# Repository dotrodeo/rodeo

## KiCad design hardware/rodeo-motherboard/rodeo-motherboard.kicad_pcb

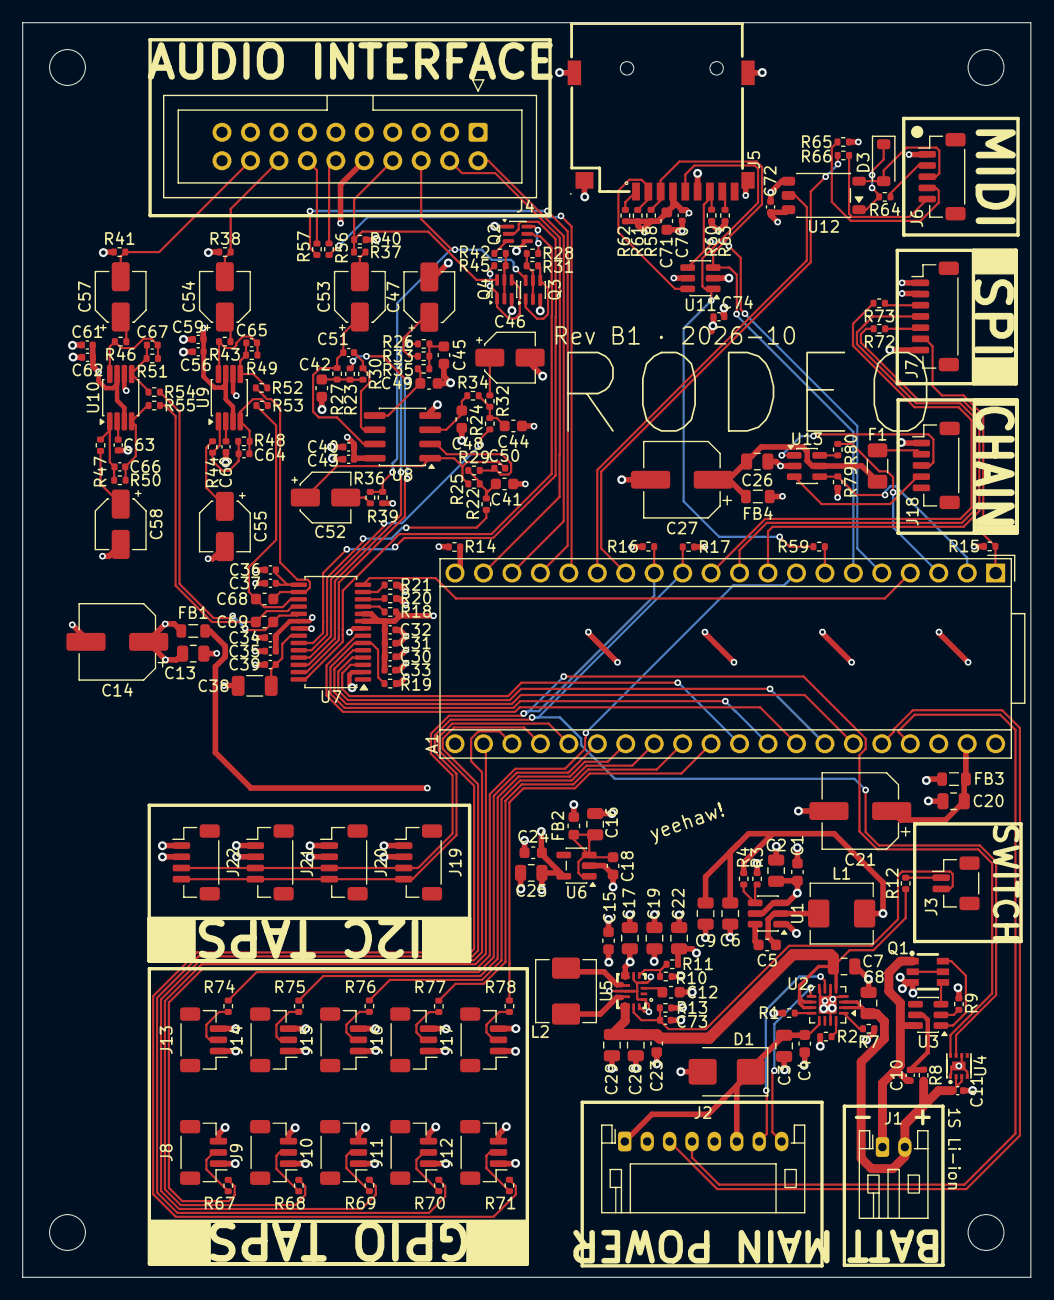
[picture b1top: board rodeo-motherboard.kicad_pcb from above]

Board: 4 copper layers, 90.0 x 112.0 mm, 205 parts (0 on the bottom side), 147 nets.

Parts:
A1: Electrosmith_Daisy_Seed_Rev4; Electrosmith_Daisy_Seed
C1, C5: 0.1u; C_0603_1608Metric
C2, C3, C13, C16, C20, C25, C26, C28, C29: 10u; C_0805_2012Metric
C4, C18, C24: 1u; C_0603_1608Metric
C6, C9, C17, C19, C22: 22u; C_0805_2012Metric
C7, C8: 4.7u; C_0805_2012Metric
C10, C30, C32, C34, C37, C39, C43, C59, C60, C62, C63, C70, C72, C74: 0.1u; C_0402_1005Metric
C11, C31, C33, C35, C36, C40, C56, C61: 1u; C_0402_1005Metric
C12: 100n; C_0603_1608Metric
C14, C21, C27: 100u; CP_Elec_6.3x5.4
C15, C23, C71: 10u; C_0603_1608Metric
C38: 47u; C_1206_3216Metric
C41, C42: 2.2n; C_0603_1608Metric
C44, C45: 6.8n; C_0603_1608Metric
C46, C47, C52, C53: 22u; CP_Elec_4x5.4
C48, C49: 1.5n; C_0603_1608Metric
C50, C51: 470p; C_0402_1005Metric
C54, C55, C57, C58: 10u; CP_Elec_4x5.4
C64, C65, C66, C67: 150p; C_0402_1005Metric
C68, C69: 2.7n; C_0603_1608Metric
C73: 10n; C_0402_1005Metric
D1: SMBJ5.0A; D_SMB
D3: 1N4148W; D_SOD-123
F1: nSMD075; Fuse_1206_3216Metric
FB1, FB3, FB4: BLM21PG221SN1D; L_0805_2012Metric
FB2: BLM18KG601SN1D; L_0603_1608Metric
H1, H2, H3, H4: MountingHole; MountingHole_3.2mm_M3
J1: Conn_01x02; JST_PH_S2B-PH-K_1x02_P2.00mm_Horizontal
J2: Conn_01x08; JST_PH_S8B-PH-K_1x08_P2.00mm_Horizontal
J3: Conn_01x02; JST_SH_BM02B-SRSS-TB_1x02-1MP_P1.00mm_Vertical
J4: Conn_02x10_Odd_Even; IDC-Header_2x10_P2.54mm_Vertical
J5: TF PUSH; TF-SMD_TF-PUSH
J6, J18: Conn_01x05; JST_SH_BM05B-SRSS-TB_1x05-1MP_P1.00mm_Vertical
J7: Conn_01x07; JST_SH_BM07B-SRSS-TB_1x07-1MP_P1.00mm_Vertical
J8, J9, J10, J11, J12, J13, J14, J15, J16, J17: Conn_01x03; JST_SH_BM03B-SRSS-TB_1x03-1MP_P1.00mm_Vertical
J19, J20, J21, J22: Conn_01x04; JST_SH_BM04B-SRSS-TB_1x04-1MP_P1.00mm_Vertical
L1: 2.2uH; L_Sunlord_MWSA0518S
L2: 1.5uH; L_Sunlord_MWSA0518S
Q1: FS8205A; SOT-23-6_L2.9-W1.6-P0.95-LS2.8-BR
Q2: BSS84DW; SOT-363_SC-70-6
Q3, Q4: 2N7002DW; SOT-363_SC-70-6
R1: 1.18K; R_0402_1005Metric
R2: 1.13K; R_0402_1005Metric
R3, R7, R12, R15, R18, R20, R21, R28, R42, R79: 10K; R_0402_1005Metric
R4: 33K2; R_0402_1005Metric
R8, R56, R57, R65, R66: 100R; R_0402_1005Metric
R9, R67, R68, R69, R70, R71, R74, R75, R76, R77, R78: 1K; R_0402_1005Metric
R10: 19K1; R_0402_1005Metric
R11: 100K; R_0402_1005Metric
R13, R19, R39, R40, R58, R60, R61, R62, R63: 47K; R_0402_1005Metric
R14: 0R; R_0402_1005Metric
R16, R17: 2K2; R_0402_1005Metric
R22, R23: 4K42; R_0402_1005Metric
R24, R26: 1K33; R_0402_1005Metric
R25, R27: 4K99; R_0402_1005Metric
R29, R30: 2K32; R_0402_1005Metric
R31, R38, R41, R45: 1M; R_0402_1005Metric
R32, R33: 1K5; R_0402_1005Metric
R34, R35: 715R; R_0402_1005Metric
R36, R37: 560R; R_0402_1005Metric
R43, R44, R46, R47: 7K5; R_0402_1005Metric
R48, R49, R50, R51: 10K5; R_0402_1005Metric
R52, R53, R54, R55: 91R; R_0402_1005Metric
R59: 22R; R_0402_1005Metric
R64: 220R; R_0402_1005Metric
R72, R73, R80: 33R; R_0402_1005Metric
U1: TPS563208; TSOT-23-6
U2: BQ24073RGT; VQFN-16-1EP_3x3mm_P0.5mm_EP1.6x1.6mm
U3: DW01A; SOT-23-6
U4: MAX17048G+T10; TDFN-8_L2.0-W2.0-P0.50-BL-EP1.2
U5: TPS63070RNMR; VQFN-15_L3.0-W2.5-P0.50-BL
U6: TPS7A2033PDBVR; SOT-23-5
U7: CS4272; TSSOP-28_4.4x9.7mm_P0.65mm
U8: OPA2376xxD; SOIC-8_3.9x4.9mm_P1.27mm
U9, U10: THS4521IDGK; VSSOP-8_3x3mm_P0.65mm
U11: SRV05-4; SOT-23-6
U12: TLP2361; SO-5-6_4.55x3.7mm_P1.27mm
U13: USBLC6-2SC6; SOT-23-6

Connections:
+3V3_A: C24.2, C25.2, J7.7, J8.3, J9.3, J10.3, J11.3, J12.3, J13.3, J14.3, J15.3, J16.3, J17.3, U6.5 (OUT)
+3V3_D: C6.2, C9.2, C30.2, C31.2, C32.2, C33.2, C70.1, C71.1, C72.2, C74.1, FB4.1, J5.4 (VDD), J7.1, J19.2, J20.2, J21.2, J22.2, L1.2, R4.2, R15.2, R16.1, R17.1, R18.2, R58.1, R60.1, R61.1, R62.1, R63.1, R65.2, R79.2, U7.9 (VD), U7.10 (VL), U11.5 (VP), U12.6 (VDD)
+3V3_SAT: C26.2, C27.1, F1.2, FB4.2, U13.5 (VBUS)
+5V_A: C13.2, C14.1, C34.2, C35.2, C40.2, C43.1, C56.2, C59.1, C61.2, C62.1, FB1.2, J4.10, Q2.1 (S), Q2.4 (S), U7.20 (VA), U8.8 (V+), U9.3 (V_{S+}), U9.7 (~PD), U10.3 (V_{S+}), U10.7 (~PD)
+5V_SYS: C1.1, C2.1, C15.1, C17.1, C19.1, C22.1, FB1.1, FB2.1, FB3.1, R11.2, U1.3 (VIN), U1.5 (EN), U5.7 (Vout)
AUDIO_IN_1: A1.16 (AUDIO_IN_1), R56.1
AUDIO_IN_2: A1.17 (AUDIO_IN_2), R57.1
AUDIO_OUT_1: A1.18 (AUDIO_OUT_1), J4.2
AUDIO_OUT_2: A1.19 (AUDIO_OUT_2), J4.4
BATT_N: C10.1, J1.1, Q1.1 (S1), U3.6 (GND)
BATT_P: C8.1, C11.1, J1.2, R8.1, U2.2 (BAT), U2.3 (BAT), U4.2 (CELL), U4.3 (VDD)
BATT_VCC: C7.1, C23.1, C28.1, C29.1, R12.1, U2.5 (EN2), U2.10 (OUT), U2.11 (OUT), U5.12 (Vin)
CLK: J5.5 (CLK), R59.1, U11.1 (IO1)
CODEC2_AINA_N: C68.2, R52.1, U7.16 (AINA-)
CODEC2_AINA_P: C68.1, R53.1, U7.17 (AINA+)
CODEC2_AINB_N: C69.2, R54.1, U7.19 (AINB-)
CODEC2_AINB_P: C69.1, R55.1, U7.18 (AINB+)
CODEC2_AOUTA_N: R22.1, U7.24 (AOUTA-)
CODEC2_AOUTA_P: R24.1, U7.25 (AOUTA+)
CODEC2_AOUTB_N: R23.1, U7.27 (AOUTB-)
CODEC2_AOUTB_P: R26.1, U7.26 (AOUTB+)
CODEC2_IN_A: C54.2, J4.16, R38.2
CODEC2_IN_B: C57.2, J4.18, R41.2
CODEC2_LRCK: A1.34 (SAI2_FS), U7.4 (LRCK)
CODEC2_MCLK: A1.31 (SAI2_MCLK), U7.3 (MCLK)
CODEC2_MUTE_A: Q2.2 (G), U7.23 (~AMUTEC)
CODEC2_MUTE_B: Q2.5 (G), U7.28 (~BMUTEC)
CODEC2_OUT_A: J4.6, Q3.6 (D), R36.1, R39.1
CODEC2_OUT_B: J4.8, Q4.6 (D), R37.1, R40.1
CODEC2_RST: A1.4 (SD_DATA_1), U7.14 (~RST)
CODEC2_SCLK: A1.35 (SAI2_SCK), U7.5 (SCLK)
CODEC2_SDIN: A1.33 (SAI2_SD_A), U7.7 (SDIN)
CODEC2_SDOUT: A1.32 (SAI2_SD_B), R19.2, U7.6 (SDOUT(M/~S))
CODEC2_VCOM: C36.2, C37.2, U7.15 (VCOM)
CV_DAC1: A1.30 (DAC_OUT1), R78.2
CV_DAC2: A1.29 (DAC_OUT2), R77.2
DAISY_SCL: A1.12 (I2C1_SCL), J19.4, J20.4, J21.4, J22.4, R17.2, U4.7 (SCL)
DAISY_SDA: A1.13 (I2C1_SDA), J19.3, J20.3, J21.3, J22.3, R16.2, U4.8 (SDA)
DAT3: J5.2 (CD/DAT3), R61.2, U11.6 (IO4)
DIG_1: A1.8 (SPI1_CS), R67.2
DIG_2: A1.22 (ADC_0), R68.2
DIG_3: A1.23 (ADC_1), R69.2
DIG_4: A1.24 (ADC_2), R70.2
DIG_5: A1.25 (ADC_3), R71.2
DIG_6: A1.26 (ADC_4), R74.2
DIG_7: A1.27 (ADC_5), R75.2
DIG_8: A1.28 (ADC_6), R76.2
GND: A1.40 (DGND), C1.2, C2.2, C3.2, C4.2, C6.1, C7.2, C8.2, C9.1, C11.2, C12.2, C13.1, C14.2, C15.2, C16.1, C17.2, C18.1, C19.2, C20.1, C21.2, C22.2, C23.2, C24.1, C25.1, C26.1, C27.2, C28.2, C29.2, C30.1, C31.1, C32.1, C33.1, C34.1, C35.1, C36.1, C37.1, C38.2, C39.1, C40.1, C41.2, C42.2, C43.2, C44.1, C45.1, C46.2, C47.2, C48.2, C49.2, C55.2, C56.1, C58.2, C59.2, C60.2, C61.1, C62.2, C63.2, C70.2, C71.2, C72.1, C73.1, C74.2, D1.2 (A), J2.2, J2.5, J4.1, J4.3, J4.5, J4.7, J4.9, J4.11, J4.13, J4.15, J4.17, J4.19, J5.6 (VSS), J5.10, J5.11, J5.12, J5.13, J6.1, J7.2, J8.1, J9.1, J10.1, J11.1, J12.1, J13.1, J14.1, J15.1, J16.1, J17.1, J18.1, J19.1, J20.1, J21.1, J22.1, Q1.3 (S2), Q3.3 (D), Q4.3 (D), R1.1, R2.1, R3.1, R7.2, R9.2, R10.1, R13.2, R14.1, R19.1, R20.2, R21.2, R38.1, R39.2, R40.2, R41.1, U1.1 (GND), U2.4 (~CE), U2.6 (EN1), U2.8 (VSS), U2.15 (TD), U2.17 (VSS), U4.1 (CTG), U4.4 (GND), U4.6 (QSTRT), U4.9 (EP), U5.1 (PS/SYNC), U5.4 (GND), U5.6 (FB2), U5.10 (PGND), U5.15 (Vsel), U6.2 (GND), U7.2 (XTI), U7.8 (DGND), U7.21 (AGND), U8.4 (V-), U9.6 (V_{S-}), U10.6 (V_{S-}), U11.2 (VN), U12.4 (GND), U13.2 (GND)
GNDA: A1.20 (AGND), R14.2
JACK_IN_1: J4.12, R56.2
JACK_IN_2: J4.14, R57.2
MIDI_IN_R: J6.2, R64.1
MIDI_IN_T: D3.2 (A), J6.3, U12.3 (K)
MIDI_OUT_R: J6.4, R65.1
MIDI_OUT_T: J6.5, R66.1
MIDI_RX: A1.15 (USART1_RX), U12.5 (VO)
MIDI_TX: A1.14 (USART1_TX), R66.2
unnamed: C41.1, R22.2, R25.1, R29.1
unnamed: C42.1, R23.2, R27.1, R30.1
unnamed: C44.2, R24.2, R32.2, R34.2
unnamed: C45.2, R26.2, R33.2, R35.2
unnamed: C46.1, R32.1
unnamed: C47.1, R33.1
unnamed: C50.1, C52.1, R25.2, U8.1
unnamed: C51.1, C53.1, R27.2, U8.7
unnamed: C52.2, R36.2
unnamed: C53.2, R37.2
unnamed: C54.1, R43.1
unnamed: C55.1, R44.1
unnamed: C57.1, R46.1
unnamed: C58.1, R47.1
unnamed: C64.2, R48.2, R53.2, U9.4
unnamed: C65.1, R49.2, R52.2, U9.5
unnamed: C66.2, R50.2, R55.2, U10.4
unnamed: C67.1, R51.2, R54.2, U10.5
unnamed: D3.1 (K), R64.2, U12.1 (A)
unnamed: J3.1, R12.2
unnamed: C73.2, J3.2, R13.1, U5.14 (EN)
unnamed: J5.8 (DAT1), R63.2
unnamed: J5.1 (DAT2), R62.2
unnamed: J7.3, R73.1
unnamed: J7.5, R72.1
unnamed: J8.2, R67.1
unnamed: J9.2, R68.1
unnamed: J10.2, R69.1
unnamed: J11.2, R70.1
unnamed: J12.2, R71.1
unnamed: J13.2, R74.1
unnamed: J14.2, R75.1
unnamed: J15.2, R76.1
unnamed: J16.2, R77.1
unnamed: J17.2, R78.1
unnamed: F1.1, J18.2
unnamed: J18.3, U13.1 (I/O1)
unnamed: J18.4, U13.3 (I/O2)
unnamed: Q1.2 (D1/D2), Q1.5 (D1/D2)
unnamed: Q1.6 (G1), U3.1 (OD)
unnamed: Q1.4 (G2), U3.3 (OC)
unnamed: Q2.6 (D), R28.2
unnamed: Q2.3 (D), R42.2
unnamed: Q3.2 (G), Q3.5 (G), R28.1, R31.1
unnamed: Q3.1 (S), Q3.4 (S), R31.2
unnamed: Q4.2 (G), Q4.5 (G), R42.1, R45.1
unnamed: Q4.1 (S), Q4.4 (S), R45.2
unnamed: R80.1, U13.6 (I/O1)
unnamed: C5.2, L1.1, U1.2 (SW)
unnamed: C5.1, U1.6 (VBST)
unnamed: R3.2, R4.1, U1.4 (VFB)
unnamed: R1.2, U2.12 (ILIM)
unnamed: R2.2, U2.16 (ISET)
unnamed: R7.1, U2.1 (TS)
unnamed: R9.1, U3.2 (CS)
unnamed: C10.2, R8.2, U3.5 (VCC)
unnamed: R10.2, R11.1, U5.5 (FB)
unnamed: L2.1, U5.11 (L1)
unnamed: L2.2, U5.9 (L2)
unnamed: C12.1, U5.3 (Vaux)
unnamed: C16.2, C18.2, FB2.2, U6.1 (IN), U6.3 (EN)
unnamed: R21.1, U7.13 (AD0/~CS(I2S/~LJ))
unnamed: C38.1, C39.2, U7.22 (FILT+)
unnamed: R18.1, U7.11 (SCL/CCLK(M0))
unnamed: R20.1, U7.12 (SDA/CDIN(M1))
unnamed: C48.1, R34.1, U8.3 (+)
unnamed: C50.2, R29.2, U8.2 (-)
unnamed: C49.1, R35.1, U8.5 (+)
unnamed: C51.2, R30.2, U8.6 (-)
unnamed: C65.2, R43.2, R49.1, U9.8 (+)
unnamed: C64.1, R44.2, R48.1, U9.1 (-)
unnamed: C60.1, U9.2 (V_{OCM})
unnamed: C67.2, R46.2, R51.1, U10.8 (+)
unnamed: C66.1, R47.2, R50.1, U10.1 (-)
unnamed: C63.1, U10.2 (V_{OCM})
SAT_RX: A1.2 (SD_DATA_3), R79.1, U13.4 (I/O2)
SAT_TX: A1.3 (SD_DATA_2), R80.2
SD_CLK: A1.7 (SD_CLK), R59.2
SD_CMD: A1.6 (SD_CMD), J5.3 (CMD), R58.2, U11.3 (IO2)
SD_D_0: A1.5 (SD_DATA_0), J5.7 (DAT0), R60.2, U11.4 (IO3)
SEED_VIN: A1.39 (VIN), C20.2, C21.1, FB3.2
SPI_EXT_CS: A1.1 (USB_ID), J7.6, R15.1
SPI_MISO: A1.10 (SPI1_POCI), J7.4
SPI_MOSI: A1.11 (SPI1_PICO), R73.2
SPI_SCK: A1.9 (SPI1_SCK), R72.2
USB_OTG_HS_N: A1.36 (USB_D_-), J2.3
USB_OTG_HS_P: A1.37 (USB_D_+), J2.4
VIN: C3.1, C4.1, D1.1 (K), J2.1, J2.6, U2.13 (IN)
~CHG: J2.8, U2.9 (~CHG)
~PGOOD: J2.7, U2.7 (~PGOOD)

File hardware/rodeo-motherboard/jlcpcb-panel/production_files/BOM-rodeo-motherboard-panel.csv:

Comment,Designator,Footprint,LCSC,Quantity
0.1u,"C1_0,C1_1,C1_2,C1_3,C5_0,C5_1,C5_2,C5_3",C_0603_1608Metric,C14663,8
10u,"C2_0,C2_1,C2_2,C2_3,C3_0,C3_1,C3_2,C3_3,C13_0,C13_1,C13_2,C13_3,C16_0,C16_1,C16_2,C16_3,C20_0,C20_1,C20_2,C20_3,C25_0,C25_1,C25_2,C25_3,C26_0,C26_1,C26_2,C26_3,C28_0,C28_1,C28_2,C28_3,C29_0,C29_1,C29_2,C29_3",C_0805_2012Metric,C15850,36
1u,"C4_0,C4_1,C4_2,C4_3,C18_0,C18_1,C18_2,C18_3,C24_0,C24_1,C24_2,C24_3",C_0603_1608Metric,C15849,12
22u,"C6_0,C6_1,C6_2,C6_3,C9_0,C9_1,C9_2,C9_3,C17_0,C17_1,C17_2,C17_3,C19_0,C19_1,C19_2,C19_3,C22_0,C22_1,C22_2,C22_3",C_0805_2012Metric,C45783,20
4.7u,"C7_0,C7_1,C7_2,C7_3,C8_0,C8_1,C8_2,C8_3",C_0805_2012Metric,C1779,8
0.1u,"C10_0,C10_1,C10_2,C10_3,C30_0,C30_1,C30_2,C30_3,C32_0,C32_1,C32_2,C32_3,C34_0,C34_1,C34_2,C34_3,C37_0,C37_1,C37_2,C37_3,C39_0,C39_1,C39_2,C39_3,C43_0,C43_1,C43_2,C43_3,C59_0,C59_1,C59_2,C59_3,C60_0,C60_1,C60_2,C60_3,C62_0,C62_1,C62_2,C62_3,C63_0,C63_1,C63_2,C63_3,C70_0,C70_1,C70_2,C70_3,C72_0,C72_1,C72_2,C72_3,C74_0,C74_1,C74_2,C74_3",C_0402_1005Metric,C1525,56
1u,"C11_0,C11_1,C11_2,C11_3,C31_0,C31_1,C31_2,C31_3,C33_0,C33_1,C33_2,C33_3,C35_0,C35_1,C35_2,C35_3,C36_0,C36_1,C36_2,C36_3,C40_0,C40_1,C40_2,C40_3,C56_0,C56_1,C56_2,C56_3,C61_0,C61_1,C61_2,C61_3",C_0402_1005Metric,C52923,32
100n,"C12_0,C12_1,C12_2,C12_3",C_0603_1608Metric,C14663,4
100u,"C14_0,C14_1,C14_2,C14_3,C21_0,C21_1,C21_2,C21_3,C27_0,C27_1,C27_2,C27_3",CP_Elec_6.3x5.4,C2887276,12
10u,"C15_0,C15_1,C15_2,C15_3,C23_0,C23_1,C23_2,C23_3,C71_0,C71_1,C71_2,C71_3",C_0603_1608Metric,C96446,12
47u,"C38_0,C38_1,C38_2,C38_3",C_1206_3216Metric,C96123,4
2.2n,"C41_0,C41_1,C41_2,C41_3,C42_0,C42_1,C42_2,C42_3",C_0603_1608Metric,C296055,8
6.8n,"C44_0,C44_1,C44_2,C44_3,C45_0,C45_1,C45_2,C45_3",C_0603_1608Metric,C513559,8
22u,"C46_0,C46_1,C46_2,C46_3,C47_0,C47_1,C47_2,C47_3,C52_0,C52_1,C52_2,C52_3,C53_0,C53_1,C53_2,C53_3",CP_Elec_4x5.4,C72502,16
1.5n,"C48_0,C48_1,C48_2,C48_3,C49_0,C49_1,C49_2,C49_3",C_0603_1608Metric,C107039,8
470p,"C50_0,C50_1,C50_2,C50_3,C51_0,C51_1,C51_2,C51_3",C_0402_1005Metric,C106259,8
10u,"C54_0,C54_1,C54_2,C54_3,C55_0,C55_1,C55_2,C55_3,C57_0,C57_1,C57_2,C57_3,C58_0,C58_1,C58_2,C58_3",CP_Elec_4x5.4,C72484,16
150p,"C64_0,C64_1,C64_2,C64_3,C65_0,C65_1,C65_2,C65_3,C66_0,C66_1,C66_2,C66_3,C67_0,C67_1,C67_2,C67_3",C_0402_1005Metric,C541469,16
2.7n,"C68_0,C68_1,C68_2,C68_3,C69_0,C69_1,C69_2,C69_3",C_0603_1608Metric,C388043,8
10n,"C73_0,C73_1,C73_2,C73_3",C_0402_1005Metric,C15195,4
SMBJ5.0A,"D1_0,D1_1,D1_2,D1_3",D_SMB,C113974,4
1N4148W,"D3_0,D3_1,D3_2,D3_3",D_SOD-123,C81598,4
nSMD075,"F1_0,F1_1,F1_2,F1_3",Fuse_1206_3216Metric,C70078,4
BLM21PG221SN1D,"FB1_0,FB1_1,FB1_2,FB1_3,FB3_0,FB3_1,FB3_2,FB3_3,FB4_0,FB4_1,FB4_2,FB4_3",L_0805_2012Metric,C85840,12
BLM18KG601SN1D,"FB2_0,FB2_1,FB2_2,FB2_3",L_0603_1608Metric,C85833,4
Conn_01x02,"J1_0,J1_1,J1_2,J1_3",JST_PH_S2B-PH-K_1x02_P2.00mm_Horizontal,C173752,4
Conn_01x08,"J2_0,J2_1,J2_2,J2_3",JST_PH_S8B-PH-K_1x08_P2.00mm_Horizontal,C157915,4
Conn_01x02,"J3_0,J3_1,J3_2,J3_3",JST_SH_BM02B-SRSS-TB_1x02-1MP_P1.00mm_Vertical,C160388,4
Conn_02x10_Odd_Even,"J4_0,J4_1,J4_2,J4_3",IDC-Header_2x10_P2.54mm_Vertical,C2977593,4
TF PUSH,"J5_0,J5_1,J5_2,J5_3",TF-SMD_TF-PUSH,C393941,4
Conn_01x05,"J6_0,J6_1,J6_2,J6_3,J18_0,J18_1,J18_2,J18_3",JST_SH_BM05B-SRSS-TB_1x05-1MP_P1.00mm_Vertical,C160391,8
Conn_01x07,"J7_0,J7_1,J7_2,J7_3",JST_SH_BM07B-SRSS-TB_1x07-1MP_P1.00mm_Vertical,C160393,4
Conn_01x03,"J8_0,J8_1,J8_2,J8_3,J9_0,J9_1,J9_2,J9_3,J10_0,J10_1,J10_2,J10_3,J11_0,J11_1,J11_2,J11_3,J12_0,J12_1,J12_2,J12_3,J13_0,J13_1,J13_2,J13_3,J14_0,J14_1,J14_2,J14_3,J15_0,J15_1,J15_2,J15_3,J16_0,J16_1,J16_2,J16_3,J17_0,J17_1,J17_2,J17_3",JST_SH_BM03B-SRSS-TB_1x03-1MP_P1.00mm_Vertical,C160389,40
Conn_01x04,"J19_0,J19_1,J19_2,J19_3,J20_0,J20_1,J20_2,J20_3,J21_0,J21_1,J21_2,J21_3,J22_0,J22_1,J22_2,J22_3",JST_SH_BM04B-SRSS-TB_1x04-1MP_P1.00mm_Vertical,C160390,16
2.2uH,"L1_0,L1_1,L1_2,L1_3",L_Sunlord_MWSA0518S,C408345,4
1.5uH,"L2_0,L2_1,L2_2,L2_3",L_Sunlord_MWSA0518S,C408344,4
FS8205A,"Q1_0,Q1_1,Q1_2,Q1_3",SOT-23-6_L2.9-W1.6-P0.95-LS2.8-BR,C2830320,4
BSS84DW,"Q2_0,Q2_1,Q2_2,Q2_3",SOT-363_SC-70-6,C161617,4
2N7002DW,"Q3_0,Q3_1,Q3_2,Q3_3,Q4_0,Q4_1,Q4_2,Q4_3",SOT-363_SC-70-6,C83571,8
1.18K,"R1_0,R1_1,R1_2,R1_3",R_0402_1005Metric,C270651,4
1.13K,"R2_0,R2_1,R2_2,R2_3",R_0402_1005Metric,C67014,4
10K,"R3_0,R3_1,R3_2,R3_3,R7_0,R7_1,R7_2,R7_3,R12_0,R12_1,R12_2,R12_3,R15_0,R15_1,R15_2,R15_3,R18_0,R18_1,R18_2,R18_3,R20_0,R20_1,R20_2,R20_3,R21_0,R21_1,R21_2,R21_3,R28_0,R28_1,R28_2,R28_3,R42_0,R42_1,R42_2,R42_3,R79_0,R79_1,R79_2,R79_3",R_0402_1005Metric,C25744,40
33K2,"R4_0,R4_1,R4_2,R4_3",R_0402_1005Metric,C122548,4
100R,"R8_0,R8_1,R8_2,R8_3,R56_0,R56_1,R56_2,R56_3,R57_0,R57_1,R57_2,R57_3,R65_0,R65_1,R65_2,R65_3,R66_0,R66_1,R66_2,R66_3",R_0402_1005Metric,C25076,20
1K,"R9_0,R9_1,R9_2,R9_3,R67_0,R67_1,R67_2,R67_3,R68_0,R68_1,R68_2,R68_3,R69_0,R69_1,R69_2,R69_3,R70_0,R70_1,R70_2,R70_3,R71_0,R71_1,R71_2,R71_3,R74_0,R74_1,R74_2,R74_3,R75_0,R75_1,R75_2,R75_3,R76_0,R76_1,R76_2,R76_3,R77_0,R77_1,R77_2,R77_3,R78_0,R78_1,R78_2,R78_3",R_0402_1005Metric,C11702,44
19K1,"R10_0,R10_1,R10_2,R10_3",R_0402_1005Metric,C52036,4
100K,"R11_0,R11_1,R11_2,R11_3",R_0402_1005Metric,C25741,4
47K,"R13_0,R13_1,R13_2,R13_3,R19_0,R19_1,R19_2,R19_3,R39_0,R39_1,R39_2,R39_3,R40_0,R40_1,R40_2,R40_3,R58_0,R58_1,R58_2,R58_3,R60_0,R60_1,R60_2,R60_3,R61_0,R61_1,R61_2,R61_3,R62_0,R62_1,R62_2,R62_3,R63_0,R63_1,R63_2,R63_3",R_0402_1005Metric,C25792,36
0R,"R14_0,R14_1,R14_2,R14_3",R_0402_1005Metric,C17168,4
2K2,"R16_0,R16_1,R16_2,R16_3,R17_0,R17_1,R17_2,R17_3",R_0402_1005Metric,C25879,8
4K42,"R22_0,R22_1,R22_2,R22_3,R23_0,R23_1,R23_2,R23_3",R_0402_1005Metric,C52269,8
1K33,"R24_0,R24_1,R24_2,R24_3,R26_0,R26_1,R26_2,R26_3",R_0402_1005Metric,C423242,8
4K99,"R25_0,R25_1,R25_2,R25_3,R27_0,R27_1,R27_2,R27_3",R_0402_1005Metric,C25903,8
2K32,"R29_0,R29_1,R29_2,R29_3,R30_0,R30_1,R30_2,R30_3",R_0402_1005Metric,C82297,8
1M,"R31_0,R31_1,R31_2,R31_3,R38_0,R38_1,R38_2,R38_3,R41_0,R41_1,R41_2,R41_3,R45_0,R45_1,R45_2,R45_3",R_0402_1005Metric,C26083,16
1K5,"R32_0,R32_1,R32_2,R32_3,R33_0,R33_1,R33_2,R33_3",R_0402_1005Metric,C25867,8
715R,"R34_0,R34_1,R34_2,R34_3,R35_0,R35_1,R35_2,R35_3",R_0402_1005Metric,C113474,8
560R,"R36_0,R36_1,R36_2,R36_3,R37_0,R37_1,R37_2,R37_3",R_0402_1005Metric,C25126,8
7K5,"R43_0,R43_1,R43_2,R43_3,R44_0,R44_1,R44_2,R44_3,R46_0,R46_1,R46_2,R46_3,R47_0,R47_1,R47_2,R47_3",R_0402_1005Metric,C25918,16
10K5,"R48_0,R48_1,R48_2,R48_3,R49_0,R49_1,R49_2,R49_3,R50_0,R50_1,R50_2,R50_3,R51_0,R51_1,R51_2,R51_3",R_0402_1005Metric,C25850,16
91R,"R52_0,R52_1,R52_2,R52_3,R53_0,R53_1,R53_2,R53_3,R54_0,R54_1,R54_2,R54_3,R55_0,R55_1,R55_2,R55_3",R_0402_1005Metric,C270574,16
22R,"R59_0,R59_1,R59_2,R59_3",R_0402_1005Metric,C25092,4
220R,"R64_0,R64_1,R64_2,R64_3",R_0402_1005Metric,C25091,4
33R,"R72_0,R72_1,R72_2,R72_3,R73_0,R73_1,R73_2,R73_3,R80_0,R80_1,R80_2,R80_3",R_0402_1005Metric,C25105,12
TPS563208,"U1_0,U1_1,U1_2,U1_3",TSOT-23-6,C468250,4
BQ24073RGT,"U2_0,U2_1,U2_2,U2_3",VQFN-16-1EP_3x3mm_P0.5mm_EP1.6x1.6mm,C15220,4
DW01A,"U3_0,U3_1,U3_2,U3_3",SOT-23-6,C351410,4
MAX17048G+T10,"U4_0,U4_1,U4_2,U4_3",TDFN-8_L2.0-W2.0-P0.50-BL-EP1.2,C2682616,4
TPS63070RNMR,"U5_0,U5_1,U5_2,U5_3",VQFN-15_L3.0-W2.5-P0.50-BL,C109322,4
TPS7A2033PDBVR,"U6_0,U6_1,U6_2,U6_3",SOT-23-5,C2862740,4
CS4272,"U7_0,U7_1,U7_2,U7_3",TSSOP-28_4.4x9.7mm_P0.65mm,C2151111,4
OPA2376xxD,"U8_0,U8_1,U8_2,U8_3",SOIC-8_3.9x4.9mm_P1.27mm,C46316,4
THS4521IDGK,"U9_0,U9_1,U9_2,U9_3,U10_0,U10_1,U10_2,U10_3",VSSOP-8_3x3mm_P0.65mm,C170157,8
SRV05-4,"U11_0,U11_1,U11_2,U11_3",SOT-23-6,C13612,4
TLP2361,"U12_0,U12_1,U12_2,U12_3",SO-5-6_4.55x3.7mm_P1.27mm,C107626,4
USBLC6-2SC6,"U13_0,U13_1,U13_2,U13_3",SOT-23-6,C7519,4

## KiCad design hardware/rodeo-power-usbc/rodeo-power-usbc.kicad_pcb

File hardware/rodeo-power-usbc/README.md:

# Rodeo power board: USB-C

The default Rev B power input: a USB-C jack on a small board behind the panel,
cabled to the motherboard's power input (J2). It carries 5 V, USB data for the
Seed (USB-MIDI, audio, DFU flashing) and the charger's status LEDs. The
contract it meets is in [`rev-b.md`, "Power"](../rodeo-motherboard/docs/rev-b.md#power).

Designed 2026-10-12. Mounting: the jack and the LEDs sit on the I/O edge and come
through panel cut-outs; the 40 × 20 mm board sits on the
[rear rail](../mounting/README.md) on two M3 × 8 mm standoffs.

## Connections

**J1, USB-C receptacle (HRO TYPE-C-31-M-12, C165948).** Symbol
`Connector:USB_C_Receptacle_USB2.0_16P`, footprint
`Connector_USB:USB_C_Receptacle_HRO_TYPE-C-31-M-12`.

| J1 pin | Net | Notes |
|---|---|---|
| A4, A9, B4, B9 (VBUS) | `VBUS` | |
| A1, A12, B1, B12 (GND), SH (shield) | `GND` | |
| A5 (CC1) | R1 5.1 kΩ to `GND` | marks the board as a sink: 5 V only, no USB-PD |
| B5 (CC2) | R2 5.1 kΩ to `GND` | |
| A6, B6 (D+) | `USB_DP_JACK` | both rows tied, for either plug orientation |
| A7, B7 (D−) | `USB_DN_JACK` | |
| A8, B8 (SBU) | no connect | |

**Protection, at the jack.**

| Part | Connection |
|---|---|
| U1 USBLC6-2SC6 (C7519), flow-through | pin 1 ← `USB_DN_JACK`, pin 6 → `USB_DN`; pin 3 ← `USB_DP_JACK`, pin 4 → `USB_DP`; pin 5 `VBUS`; pin 2 `GND` |
| D1 SMF5.0A TVS (C193402) | cathode `VBUS`, anode `GND` |
| C1 4.7 µF 25 V 0603 (C69335) | `VBUS` to `GND` |

**J2, to the motherboard: JST PH 8-pin vertical, B8B-PH-K-S (C157974).**
Same pin numbers as the motherboard's J2, so a standard PH cable (pin 1 to
pin 1) connects them. Pin 1 is at the right as seen in KiCad (I/O edge at the
top). The motherboard's J2 faces the front of the case, so the cable leaves it
forward and folds back to this board; with pin 1 here on that side, the cable
arrives without a twist.

| J2 pin | Net |
|---|---|
| 1, 6 | `VBUS` |
| 2, 5 | `GND` |
| 3 | `USB_DN` |
| 4 | `USB_DP` |
| 7 | `~PGOOD` |
| 8 | `~CHG` |

**Status LEDs: side-view LiteOn LTST-S220, at the panel edge.** Symbol
`Device:LED`, footprint `rodeo_power:LED_LiteOn_LTST-S220_SideView`. The lens is
on the side the silkscreen bracket wraps (the courtyard bulges there too); put
that side at the board edge.

| Part | Anode | Cathode |
|---|---|---|
| D1 green LTST-S220KGKT (C160469), power good | R3 1 kΩ to `VBUS` | `~PGOOD` (J2 pin 7) |
| D2 red LTST-S220KRKT (C284935), charging | R4 1 kΩ to `VBUS` | `~CHG` (J2 pin 8) |

≈3 mA each. Both light only with USB plugged in: power good when the
motherboard's charger accepts the input, red while the cell charges.

**Mounting:** two M3 holes (`MountingHole:MountingHole_3.2mm_M3`) at (5, 15)
and (35, 15) mm from the I/O edge's left end: rail row 1, 30 mm apart.

## Parts

| Part | Qty | LCSC |
|---|---|---|
| TYPE-C-31-M-12 USB-C | 1 | C165948 |
| USBLC6-2SC6 | 1 | C7519 |
| SMF5.0A | 1 | C193402 |
| 4.7 µF 25 V 0603 | 1 | C69335 |
| 5.1 kΩ 0402 | 2 | C25905 |
| 1 kΩ 0402 | 2 | C11702 |
| LTST-S220KGKT (green) | 1 | C160469 |
| LTST-S220KRKT (red) | 1 | C284935 |
| B8B-PH-K-S | 1 | C157974 |

## Layout

* J1 and both LEDs on the panel edge; J1's shell flush with the edge.
* U1 and D1 within a few mm of J1, D+/D− routed as a pair (90 Ω differential),
  short, to J2.
* The cable to the motherboard: PH 8-pin both ends, 24–26 AWG, under ≈30 cm, with
  D+/D− adjacent (they sit between the two grounds).

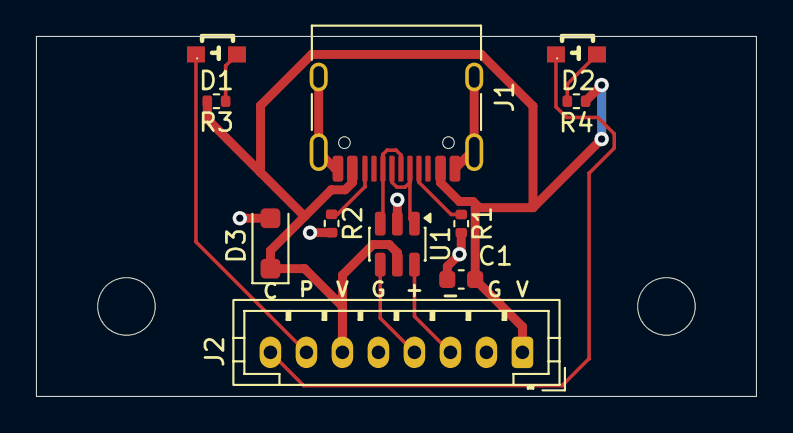
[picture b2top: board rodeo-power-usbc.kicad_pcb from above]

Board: 2 copper layers, 40.0 x 20.0 mm, 13 parts (0 on the bottom side), 12 nets.

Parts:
C1: 4.7u; C_0603_1608Metric
D1: LTST-S220KGKT; LED_LiteOn_LTST-S220_SideView
D2: LTST-S220KRKT; LED_LiteOn_LTST-S220_SideView
D3: SMF5.0A; D_SOD-123F
H1, H2: MountingHole; MountingHole_3.2mm_M3
J1: USB_C_Receptacle_USB2.0_16P; USB_C_Receptacle_HRO_TYPE-C-31-M-12
J2: Conn_01x08; JST_PH_B8B-PH-K_1x08_P2.00mm_Vertical
R1, R2: 5K1; R_0402_1005Metric
R3, R4: 1K; R_0402_1005Metric
U1: USBLC6-2SC6; SOT-23-6

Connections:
GND: C1.2, D3.2 (A), J1.A1 (GND), J1.A12 (GND), J1.B1 (GND), J1.B12 (GND), J1.SH (SHIELD), J2.2, J2.5, R1.2, R2.2, U1.2 (GND)
unnamed: D1.2 (A), R3.1
unnamed: D2.2 (A), R4.1
unnamed: J1.A5 (CC1), R1.1
unnamed: J1.B5 (CC2), R2.1
USB_DN: J2.3, U1.6 (I/O1)
USB_DN_JACK: J1.A7 (D-), J1.B7 (D-), U1.1 (I/O1)
USB_DP: J2.4, U1.4 (I/O2)
USB_DP_JACK: J1.A6 (D+), J1.B6 (D+), U1.3 (I/O2)
VBUS: C1.1, D3.1 (K), J1.A4 (VBUS), J1.A9 (VBUS), J1.B4 (VBUS), J1.B9 (VBUS), J2.1, J2.6, R3.2, R4.2, U1.5 (VBUS)
~CHG: D2.1 (K), J2.8
~PGOOD: D1.1 (K), J2.7

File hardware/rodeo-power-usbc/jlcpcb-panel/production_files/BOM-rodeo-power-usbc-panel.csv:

Comment,Designator,Footprint,LCSC,Quantity
4.7u,"C1_0,C1_1,C1_2,C1_3",C_0603_1608Metric,C69335,4
LTST-S220KGKT,"D1_0,D1_1,D1_2,D1_3",LED_LiteOn_LTST-S220_SideView,C160469,4
LTST-S220KRKT,"D2_0,D2_1,D2_2,D2_3",LED_LiteOn_LTST-S220_SideView,C284935,4
SMF5.0A,"D3_0,D3_1,D3_2,D3_3",D_SOD-123F,C193402,4
USB_C_Receptacle_USB2.0_16P,"J1_0,J1_1,J1_2,J1_3",USB_C_Receptacle_HRO_TYPE-C-31-M-12,C165948,4
Conn_01x08,"J2_0,J2_1,J2_2,J2_3",JST_PH_B8B-PH-K_1x08_P2.00mm_Vertical,C157974,4
5K1,"R1_0,R1_1,R1_2,R1_3,R2_0,R2_1,R2_2,R2_3",R_0402_1005Metric,C25905,8
1K,"R3_0,R3_1,R3_2,R3_3,R4_0,R4_1,R4_2,R4_3",R_0402_1005Metric,C11702,8
USBLC6-2SC6,"U1_0,U1_1,U1_2,U1_3",SOT-23-6,C7519,4

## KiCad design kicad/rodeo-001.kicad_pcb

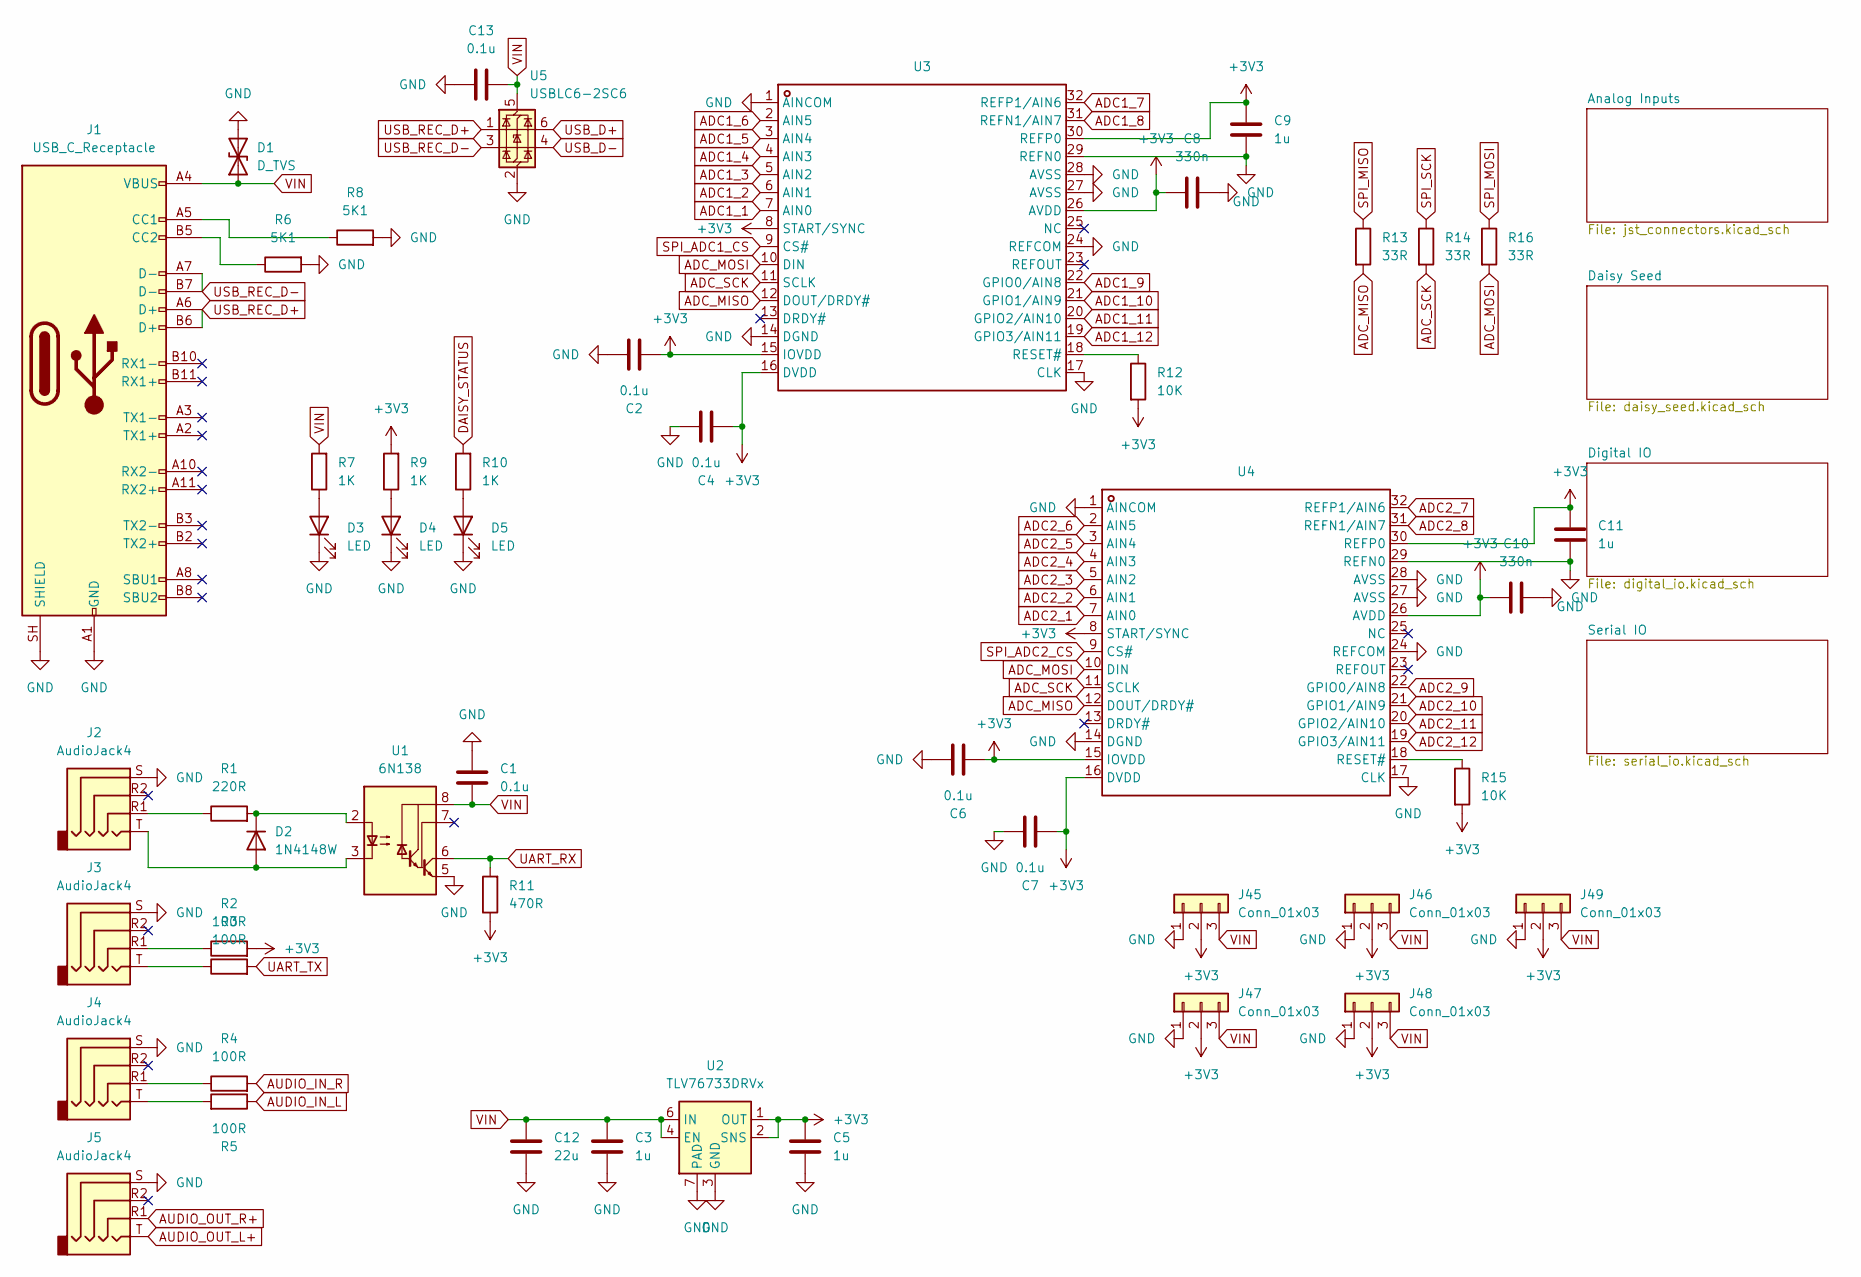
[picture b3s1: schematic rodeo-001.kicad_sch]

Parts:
C1, C2, C4, C6, C7, C13: 0.1u; C_0603_1608Metric
C3, C5: 1u; C_0805_2012Metric
C8, C10: 330n; C_0603_1608Metric
C9, C11: 1u; C_0603_1608Metric
C12: 22u; C_0805_2012Metric
D1: D_TVS; D_SOD-323
D2: 1N4148W; D_SOD-123
D3, D4, D5: LED; LED_1206_3216Metric
J1: USB_C_Receptacle; USB_C_Receptacle_GCT_USB4105-xx-A_16P_TopMnt_Horizontal
J2, J3, J4, J5: AudioJack4; Jack_3.5mm_PJ320D_Horizontal
J45, J46, J47, J48, J49: Conn_01x03; JST_ZH_B3B-ZR-SM4-TF_1x03-1MP_P1.50mm_Vertical
R1: 220R; R_0603_1608Metric
R2, R3, R4, R5: 100R; R_0603_1608Metric
R6, R8: 5K1; R_0603_1608Metric
R7, R9, R10: 1K; R_0603_1608Metric
R11: 470R; R_0603_1608Metric
R12, R15: 10K; R_0603_1608Metric
R13, R14, R16: 33R; R_0603_1608Metric
U1: 6N138; DIP-8_W7.62mm
U2: TLV76733DRVx; WSON-6-1EP_2x2mm_P0.65mm_EP1x1.6mm_ThermalVias
U3, U4: TQFP-32_L5.0-W5.0-P0.50-LS7.0-BL; Manufacturer Part ADS114S08BIPBSR; LCSC Part Name 具有PGA和电压基准的低功耗、低噪声、高集成度、6通道和12通道、4kSPS、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
U5: USBLC6-2SC6; SOT-23-6

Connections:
+3V3: C2.1, C4.1, C5.1, C6.1, C7.1, C8.1, C9.2, C10.1, C11.2, J45.2, J46.2, J47.2, J48.2, J49.2, R2.2, R9.2, R11.1, R12.2, R15.2, U2.1 (OUT), U2.2 (SNS), U3.8 (START/SYNC), U3.15 (IOVDD), U3.16 (DVDD), U3.26 (AVDD), U3.30 (REFP0), U4.8 (START/SYNC), U4.15 (IOVDD), U4.16 (DVDD), U4.26 (AVDD), U4.30 (REFP0); also elsewhere on the board
ADC1_1: U3.7 (AIN0); also elsewhere on the board
ADC1_2: U3.6 (AIN1); also elsewhere on the board
ADC1_3: U3.5 (AIN2); also elsewhere on the board
ADC1_4: U3.4 (AIN3); also elsewhere on the board
ADC1_5: U3.3 (AIN4); also elsewhere on the board
ADC1_6: U3.2 (AIN5); also elsewhere on the board
ADC1_7: U3.32 (REFP1/AIN6); also elsewhere on the board
ADC1_8: U3.31 (REFN1/AIN7); also elsewhere on the board
ADC1_9: U3.22 (GPIO0/AIN8); also elsewhere on the board
ADC1_10: U3.21 (GPIO1/AIN9); also elsewhere on the board
ADC1_11: U3.20 (GPIO2/AIN10); also elsewhere on the board
ADC1_12: U3.19 (GPIO3/AIN11); also elsewhere on the board
ADC2_1: U4.7 (AIN0); also elsewhere on the board
ADC2_2: U4.6 (AIN1); also elsewhere on the board
ADC2_3: U4.5 (AIN2); also elsewhere on the board
ADC2_4: U4.4 (AIN3); also elsewhere on the board
ADC2_5: U4.3 (AIN4); also elsewhere on the board
ADC2_6: U4.2 (AIN5); also elsewhere on the board
ADC2_7: U4.32 (REFP1/AIN6); also elsewhere on the board
ADC2_8: U4.31 (REFN1/AIN7); also elsewhere on the board
ADC2_9: U4.22 (GPIO0/AIN8); also elsewhere on the board
ADC2_10: U4.21 (GPIO1/AIN9); also elsewhere on the board
ADC2_11: U4.20 (GPIO2/AIN10); also elsewhere on the board
ADC2_12: U4.19 (GPIO3/AIN11); also elsewhere on the board
ADC_MISO: R13.2, U3.12 (DOUT/DRDY#), U4.12 (DOUT/DRDY#)
ADC_MOSI: R16.2, U3.10 (DIN), U4.10 (DIN)
ADC_SCK: R14.2, U3.11 (SCLK), U4.11 (SCLK)
AUDIO_IN_L: R5.1; also elsewhere on the board
AUDIO_IN_R: R4.2; also elsewhere on the board
AUDIO_OUT_L+: J5.T; also elsewhere on the board
AUDIO_OUT_R+: J5.R1; also elsewhere on the board
DAISY_STATUS: R10.2; also elsewhere on the board
GND: C1.1, C2.2, C3.2, C4.2, C5.2, C6.2, C7.2, C8.2, C9.1, C10.2, C11.1, C12.2, C13.1, D1.2 (A2), D3.1 (K), D4.1 (K), D5.1 (K), J1.A1 (GND), J1.A12 (GND), J1.B1 (GND), J1.B12 (GND), J1.SH (SHIELD), J2.S, J3.S, J4.S, J5.S, J45.1, J46.1, J47.1, J48.1, J49.1, R6.2, R8.2, U1.5 (GND), U2.3 (GND), U2.5 (GND), U2.7 (PAD), U3.1 (AINCOM), U3.14 (DGND), U3.17 (CLK), U3.24 (REFCOM), U3.27 (AVSS), U3.28 (AVSS), U3.29 (REFN0), U4.1 (AINCOM), U4.14 (DGND), U4.17 (CLK), U4.24 (REFCOM), U4.27 (AVSS), U4.28 (AVSS), U4.29 (REFN0), U5.2 (GND); also elsewhere on the board
unnamed: D2.2 (A), J2.T, U1.3 (C2)
unnamed: D2.1 (K), R1.2, U1.2 (C1)
unnamed: D3.2 (A), R7.1
unnamed: D4.2 (A), R9.1
unnamed: D5.2 (A), R10.1
unnamed: J1.A5 (CC1), R8.1
unnamed: J1.B5 (CC2), R6.1
unnamed: J2.R1, R1.1
unnamed: J3.R1, R2.1
unnamed: J3.T, R3.1
unnamed: J4.R1, R4.1
unnamed: J4.T, R5.2
unnamed: R12.1, U3.18 (RESET#)
unnamed: R15.1, U4.18 (RESET#)
SPI_ADC1_CS: U3.9 (CS#); also elsewhere on the board
SPI_ADC2_CS: U4.9 (CS#); also elsewhere on the board
SPI_MISO: R13.1; also elsewhere on the board
SPI_MOSI: R16.1; also elsewhere on the board
SPI_SCK: R14.1; also elsewhere on the board
UART_RX: R11.2, U1.6 (VO2); also elsewhere on the board
UART_TX: R3.2; also elsewhere on the board
USB_D+: U5.6 (I/O1); also elsewhere on the board
USB_D-: U5.4 (I/O2); also elsewhere on the board
USB_REC_D+: J1.A6 (D+), J1.B6 (D+), U5.1 (I/O1)
USB_REC_D-: J1.A7 (D-), J1.B7 (D-), U5.3 (I/O2)
VIN: C1.2, C3.1, C12.1, C13.2, D1.1 (A1), J1.A4 (VBUS), J1.A9 (VBUS), J1.B4 (VBUS), J1.B9 (VBUS), J45.3, J46.3, J47.3, J48.3, J49.3, R7.2, U1.8 (VCC), U2.4 (EN), U2.6 (IN), U5.5 (VBUS); also elsewhere on the board

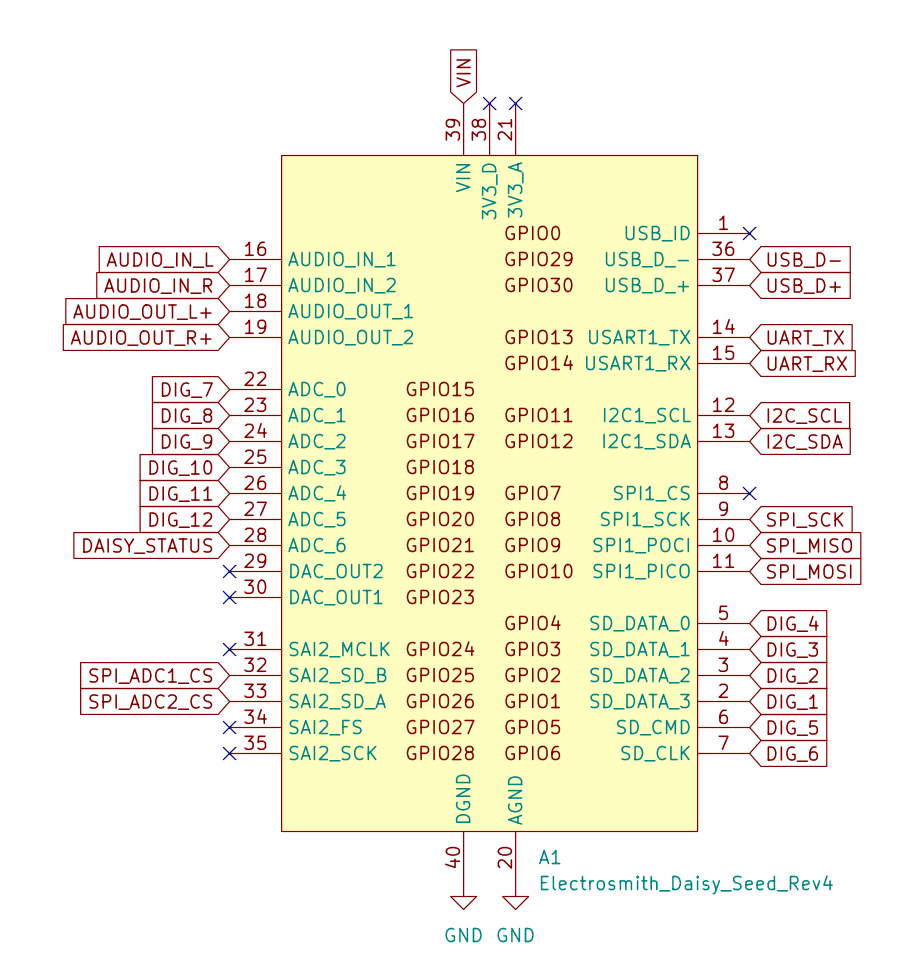
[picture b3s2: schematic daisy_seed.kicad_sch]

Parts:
A1: Electrosmith_Daisy_Seed_Rev4; Electrosmith_Daisy_Seed

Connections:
AUDIO_IN_L: A1.16 (AUDIO_IN_1); also elsewhere on the board
AUDIO_IN_R: A1.17 (AUDIO_IN_2); also elsewhere on the board
AUDIO_OUT_L+: A1.18 (AUDIO_OUT_1); also elsewhere on the board
AUDIO_OUT_R+: A1.19 (AUDIO_OUT_2); also elsewhere on the board
DAISY_STATUS: A1.28 (ADC_6); also elsewhere on the board
DIG_1: A1.2 (SD_DATA_3); also elsewhere on the board
DIG_2: A1.3 (SD_DATA_2); also elsewhere on the board
DIG_3: A1.4 (SD_DATA_1); also elsewhere on the board
DIG_4: A1.5 (SD_DATA_0); also elsewhere on the board
DIG_5: A1.6 (SD_CMD); also elsewhere on the board
DIG_6: A1.7 (SD_CLK); also elsewhere on the board
DIG_7: A1.22 (ADC_0); also elsewhere on the board
DIG_8: A1.23 (ADC_1); also elsewhere on the board
DIG_9: A1.24 (ADC_2); also elsewhere on the board
DIG_10: A1.25 (ADC_3); also elsewhere on the board
DIG_11: A1.26 (ADC_4); also elsewhere on the board
DIG_12: A1.27 (ADC_5); also elsewhere on the board
GND: A1.20 (AGND), A1.40 (DGND); also elsewhere on the board
I2C_SCL: A1.12 (I2C1_SCL); also elsewhere on the board
I2C_SDA: A1.13 (I2C1_SDA); also elsewhere on the board
SPI_ADC1_CS: A1.32 (SAI2_SD_B); also elsewhere on the board
SPI_ADC2_CS: A1.33 (SAI2_SD_A); also elsewhere on the board
SPI_MISO: A1.10 (SPI1_POCI); also elsewhere on the board
SPI_MOSI: A1.11 (SPI1_PICO); also elsewhere on the board
SPI_SCK: A1.9 (SPI1_SCK); also elsewhere on the board
UART_RX: A1.15 (USART1_RX); also elsewhere on the board
UART_TX: A1.14 (USART1_TX); also elsewhere on the board
USB_D+: A1.37 (USB_D_+); also elsewhere on the board
USB_D-: A1.36 (USB_D_-); also elsewhere on the board
VIN: A1.39 (VIN); also elsewhere on the board

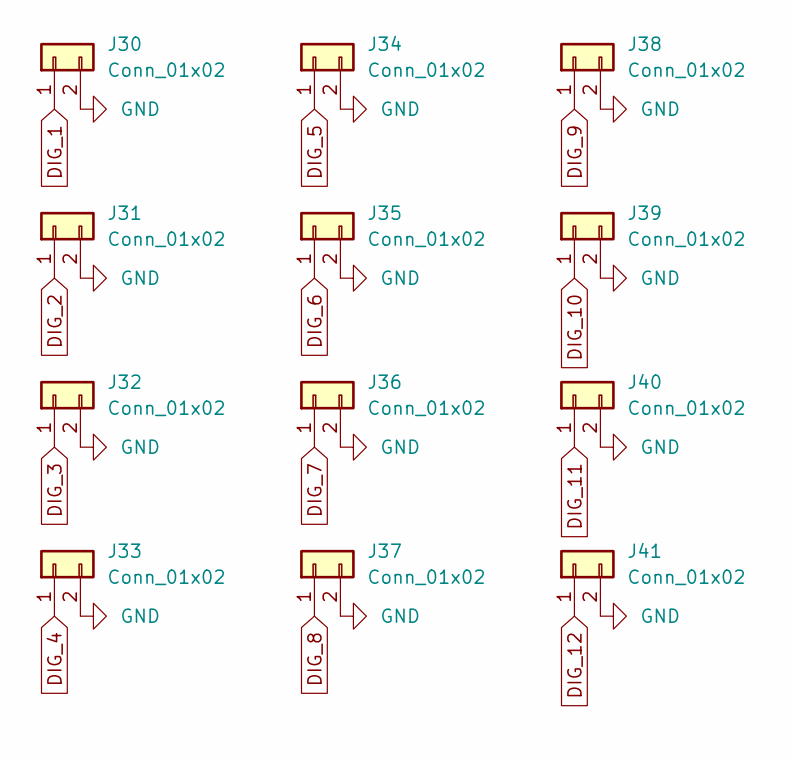
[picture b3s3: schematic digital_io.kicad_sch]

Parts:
J30, J31, J32, J33, J34, J35, J36, J37, J38, J39, J40, J41: Conn_01x02; JST_SH_BM02B-SRSS-TB_1x02-1MP_P1.00mm_Vertical

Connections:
DIG_1: J30.1; also elsewhere on the board
DIG_2: J31.1; also elsewhere on the board
DIG_3: J32.1; also elsewhere on the board
DIG_4: J33.1; also elsewhere on the board
DIG_5: J34.1; also elsewhere on the board
DIG_6: J35.1; also elsewhere on the board
DIG_7: J36.1; also elsewhere on the board
DIG_8: J37.1; also elsewhere on the board
DIG_9: J38.1; also elsewhere on the board
DIG_10: J39.1; also elsewhere on the board
DIG_11: J40.1; also elsewhere on the board
DIG_12: J41.1; also elsewhere on the board
GND: J30.2, J31.2, J32.2, J33.2, J34.2, J35.2, J36.2, J37.2, J38.2, J39.2, J40.2, J41.2; also elsewhere on the board

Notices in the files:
hardware/rodeo-motherboard/rodeo-motherboard.kicad_pcb:
© 2026 DOT RODEO LLC
CERN-OHL-W-2.0
